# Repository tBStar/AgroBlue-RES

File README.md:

# AgroBlue
When BLE meets agronomy.

My idea is very simple yet ambitious. Imagine a fleet of BLE enabled soil probes working in harmony that can sense the environment and be able to communicate with a central unit. This central unit will be responsible for collecting data for analysis.

This proof of concept is the understanding of how the combination of all sensors reading correlate to each other, to maximize efficiency and increase crop yield in the open. Battery longevity and cost are my main goals, let's hope it will work out.

1st Step:(PCB)
---------
- Get your board fabricated! The Eagle files are provided as-is, without warranty of any kind so use it at your own risk!
I used https://oshpark.com/ for my fabrication shop because I heard so many positive reviews. I initially opted for the regular service which takes 3 weeks but they upgraded me for free because they had free room on one of our Super Swift Service panels, So thank you OSH Park.
 - Get the components, I've included the BOM but I will list them here for the sake of having everything in one page.

|Qty|Description|URL|Price|
|---|---|---|---|
|x 1|Coin Cell Battery Holders Linx CR2032 Battery Holder|http://www.mouser.com/search/ProductDetail.aspx?r=712-BAT-HLD-001|$0.25|
|x 1|Lithium Ion Polymer Battery 3.7V 350mAh|https://www.arrow.com/en/products/2750/adafruit-industries|$6.77|
|x 2|Res Thin Film 0805 100 Ohm 1% 0.25W (1/4W)|https://www.arrow.com/en/products/rncp0805ftd100r/stackpole-electronics|$0.0052|
|x 1|Cap Ceramic 0.1uF 16V X7R 10% Pad SMD 0805|https://www.arrow.com/en/products/cl21b104koannnd/samsung-electro-mechanics|$0.02|
|x 1|Trans GP BJT NPN 40V 0.6A 3-Pin SOT-23|https://www.arrow.com/en/products/mmbt2222alt3g/on-semiconductor|$0.02|
|x 1|Lithium Battery Coin 3V 225mAh|https://www.arrow.com/en/products/cr-2032lbn/panasonic|$0.18|
|x 1|SparkFun ESP8266 Thing - Dev Board|https://www.sparkfun.com/products/13711|$15.95|
|x 1|HM-10 BLE Module|https://www.aliexpress.com/item/HM-10-cc2541-4-0-BLE-bluetooth-to-uart-transceiver-Module-Central-Peripheral-switching-iBeacon-AirLocate/32460585727.html|$3.34|
|x 1|HM-10 BLE Module Breakout Board|https://www.aliexpress.com/item/Free-shipping-HM-10-Bluetooth-BLE-4-0-Module-transparent-serial-port-Bluetooth-4-0-module/1913999168.html|$4.75|

2nd Step:(Optional if you have BLE Module Clones)
-------------------------------------------------
If you've gotten yourself some HM-10 clones, fear not. The following is an effective way to upload the original firmware to the module. We are going to be using v540. the original files can be found here: https://github.com/RedBearLab/CCLoader.

1. Load the CCLoader Arduino sketch to the UNO board.
2. Wire the pins:
  
3. Use CCLoader.exe to load the CC2541hm10v540.bin to the UNO board and the board will burn the firmware to the BLE Mini.

3rd Step: (Configure BLE Modules Master/Slave)
----------------------------------------------

a) Slave:
Upload an empty sketch to Aruidno and hookup the sensor module with it like this:

HM-10||Arduino
|---|---|---|
TX|<---->|TX
RX|<---->|RX
GND|<---->|GND
VCC|<---->|3.3V

Open the serial and type the following command to switch the mode of transmission to remote:
AT+MODE2: Remote Control Mode
AT+ROLE0: Peripheral Mode (Default)
AT+PWRM0: Auto Sleep
AT+ADVIF: Set the advertising interval to 7s (MAX)
AT+NAMEXXX: Where XXX is your preferred name
AT+BAUD4: Set the baud rate to 115200
AT+RESET: Restart module

b) Master
Hook up the BLE Module Breakout board the same way as the Sensor per below and type the following commands:

On master side:
AT+RENEW: Restore all setup value to factory setup
AT+IMME1: Only respond the AT Commands
AT+ROLE1: Central/Master Mode
AT+NAMEXXX: Where XXX is your preferred name
AT+BAUD4: Set the baud rate to 115200
AT+RESET: Restart module

c) Upgrade firmware on genuine BLE module (Optional)
AT+VERR?: Will give you the version
For example, you need to be at least at V526 for analog support.

**HM-10** is designed and made by **JNHuaMao Technology Company**
More info on the upgrading process, visit http://www.jnhuamao.cn/

4th Step: (Getting the ESP8266 Dev Ready)
-----------------------------------------
1- Make sure you hookup the BLE Central/Master with the ESP8266 per below because we will be using SoftSerial library.

2- Use your Cayenne/Wifi credentials and upload main.ino located in Arduino/Code folder to the ESP8266. Open the serial and set it the baud rate to match your BLE Central.
	
3- Alternatively, you can use CentalBLEConfig.ino for debuging purposes. The code echos the serial input to the BLE and vice versa.
	
4- I found hooking up a lipo battery to the Slave BLE module works best because I found 3.3V is unusually lower for this kind of circuit. Make sure you don't hookup the cell and the lipo at the same time. There is no reverse current protection.
	
5- Water your plan and you should see some reading coming through your cloud interface through channel 0.

In Summary:
-----------
I thank all the sponsors that made this contest possible. Special thanks to Sparkfun for their gratuitous dev board. I made mamy mistakes a long the way but the experience and sense of accomplishment was beyond what I imagined. I hope my work can pave the way for a continuation for finding inovative ways to improve on my design to make the world a better place.
Res stands for resistive, the probes can corrode very easily which will require replacement. As is this iteration can only be used indoor. I've done current consumption readings:
Sleep mode: 20uA
Advertising: 80uA
Connected: 8mA
Moisture Sensing: ~100mA
I found out very inefficient compared to capacitive sensing which can consume about 5mA while sensing. Very interesting indeed.

Also, to harness the full power of any BLE module is to be able to program it myself. Most of the advanced BLE modules use a flavor of ARM Cortex M processors, since they are engineered for maximum power efficiency, it makes them the rightful candidates for my next project which will be called AgroBlue-Cap.
For outdoor usage, I highly recommend you apply silicone conformal coating because the module as is can be easily damaged by environmental elements. Ideally, I would enclose the circuitry in a water/moisture proof box and use an external antenna.

Tidbits:
--------
- Sparkfun originally shipped the wrong Wifi module. They later shipped the correct one, since it was a mistake, they let me keep both.
- OshPark upgraded my order to the express service for free which costs double and take a lot less, so thank you OshPark.
- The datasheet provided by JNHuaMao Technology Company has a serious mistake. PIN3 is listed as ADC compatible while it wasn't. So bonded PIN4 to it for immediate fix, the schematics has been corrected.
- Since I was rushing to get the project out, I accidently exposed my cayenne/wifi credentials. A fatal mistake but I got a good laugh at it, so always double check and don't rush.
- I am a first timer on all levels, contest, github, eagle, board fabrication, smd soldering, youtube publishing and video recording. Quite a story there.

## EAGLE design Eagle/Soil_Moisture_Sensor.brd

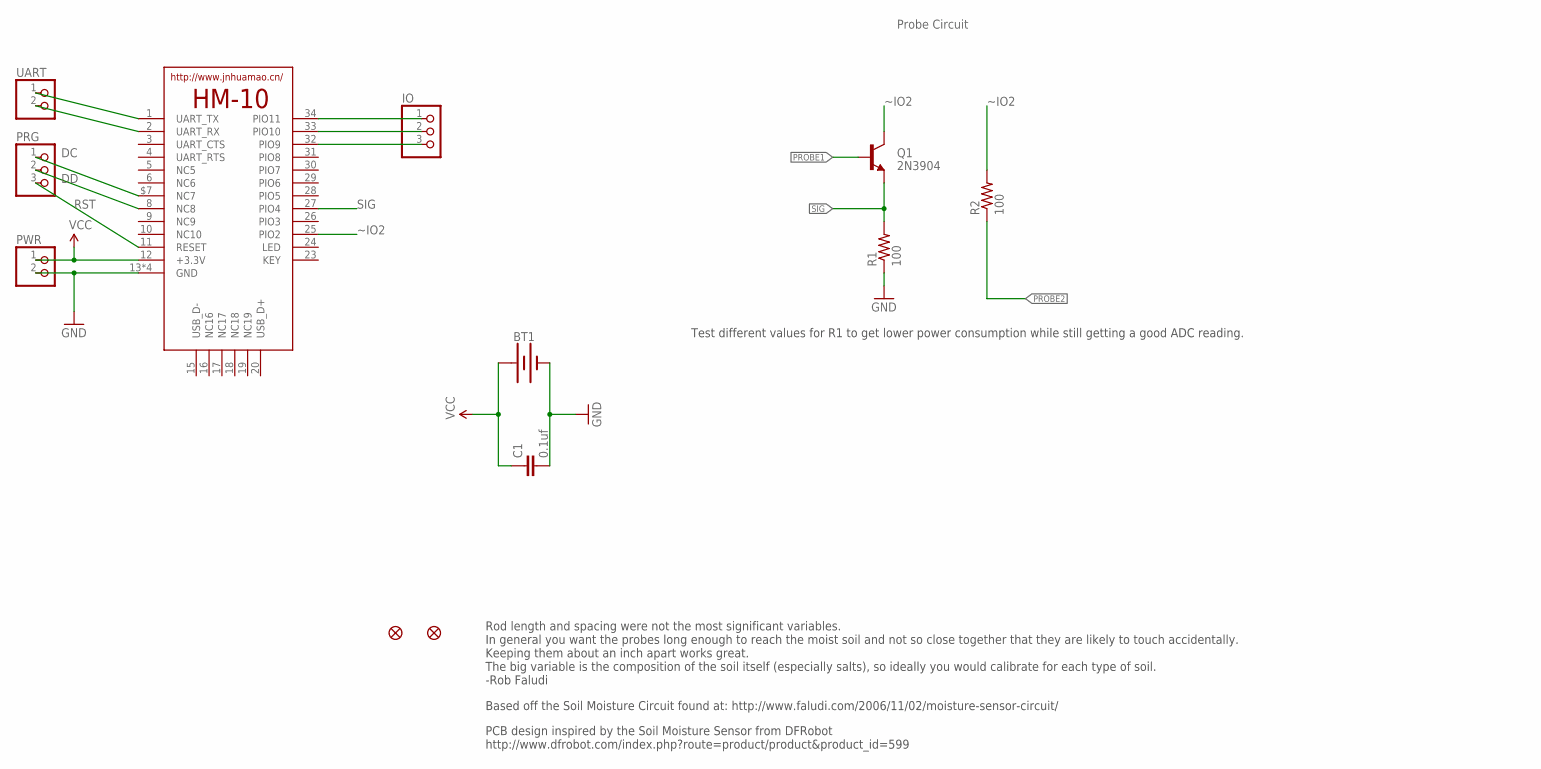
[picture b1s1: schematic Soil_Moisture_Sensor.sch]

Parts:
BT1: BATTERY-20MM_SMD_4LEGS; BATTCON_20MM_4LEGS
C1: 0.1uf; C0805
FD1, FD2: FIDUCIAL1X2; FIDUCIAL-1X2
HM-10: HM-10-BOARD; 26.9X13X2.2_BOARD
IO: PINHD-1X3; 1X03
PRG: PINHD-1X3; 1X03
PWR: PINHD-1X2; 1X02
Q1: 2N3904; SOT23-3
R1, R2: 100; R0805
UART: PINHD-1X2; 1X02

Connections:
DC: HM-10.$7 (NC7), PRG.1
DD: HM-10.8 (NC8), PRG.2
GND: BT1.NEGATIVE (-), C1.2, HM-10.13 (GND), HM-10.14 (GND), HM-10.21 (GND), HM-10.22 (GND), PWR.2, R1.1
unnamed: HM-10.34 (PIO11), IO.1
unnamed: HM-10.33 (PIO10), IO.2
unnamed: HM-10.32 (PIO9), IO.3
unnamed: HM-10.1 (UART_TX), UART.1
unnamed: HM-10.2 (UART_RX), UART.2
PROBE1: Q1.1 (B)
PROBE2: R2.1
RST: HM-10.11 (RESET), PRG.3
SIG: HM-10.27 (PIO4), Q1.2 (E), R1.2
VCC: BT1.POSITIVE@1 (+), BT1.POSITIVE@2 (+), BT1.POSITIVE@3 (+), BT1.POSITIVE@4 (+), C1.1, HM-10.12 (+3.3V), PWR.1
~IO2: HM-10.25 (PIO2), Q1.3 (C), R2.2

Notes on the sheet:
Test different values for R1 to get lower power consumption while still getting a good ADC reading.
Based off the Soil Moisture Circuit found at: http://www.faludi.com/2006/11/02/moisture-sensor-circuit/
Rod length and spacing were not the most significant variables. In general you want the probes long enough to reach the moist soil and not so close together that they are likely to touch accidentally. Keeping them about an inch apart works great. The big variable is the composition of the soil itse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
Probe Circuit
PCB design inspired by the Soil Moisture Sensor from DFRobot http://www.dfrobot.com/index.php?route=product/product&product_id=599

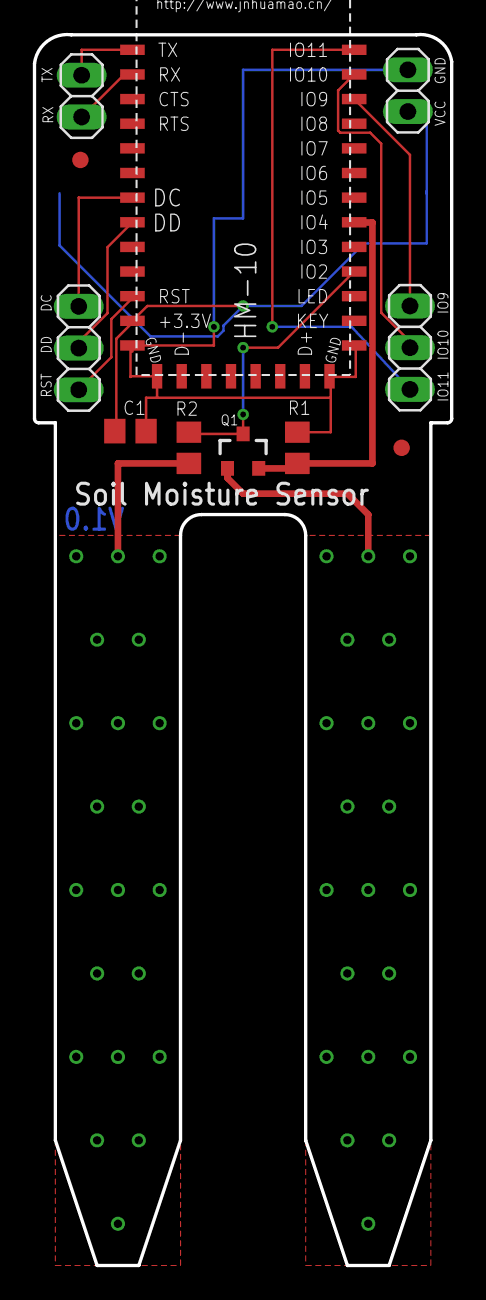
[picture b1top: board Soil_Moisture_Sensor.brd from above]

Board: 2 copper layers, 25.4 x 74.9 mm, 12 parts (1 on the bottom side), 12 nets.

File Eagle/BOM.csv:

"Part";"Value";"Device";"Package";"Description";"PROD_ID";"SF_SKU";"VALUE";
"BT1";"";"BATTERY-20MM_SMD_4LEGS";"BATTCON_20MM_4LEGS";"Battery - Single Cell";"BATT-10373";"PRT-11892";"";
"C1";"0.1uf";"C-EUC0805";"C0805";"CAPACITOR, European symbol";"";"";"";
"FD1";"FIDUCIAL1X2";"FIDUCIAL1X2";"FIDUCIAL-1X2";"Fiducial Alignment Points";"";"";"";
"FD2";"FIDUCIAL1X2";"FIDUCIAL1X2";"FIDUCIAL-1X2";"Fiducial Alignment Points";"";"";"";
"HM-10";"HM-10-BOARD";"HM-10-BOARD";"26.9X13X2.2_BOARD";"HM Bluetooth module use TI CC2540 or CC2541, Master and slave roles in one, transmission version and remote control version and PIO state acquisition functions in one, Support the AT command modify module parameters, Convenient and flexible.";"";"";"";
"IO";"";"PINHD-1X3";"1X03";"PIN HEADER";"";"";"";
"PRG";"";"PINHD-1X3";"1X03";"PIN HEADER";"";"";"";
"PWR";"";"PINHD-1X2";"1X02";"PIN HEADER";"";"";"";
"Q1";"2N3904";"TRANSISTOR_NPNMMBT2222A";"SOT23-3";"Generic NPN BJT";"TRANS-08049";"";"MMBT2222A";
"R1";"100";"100OHM-1/4W-5%(0603)";"0603-RES";"";"RES-12438";"";"100/.25W";
"R2";"100";"100OHM-1/4W-5%(0603)";"0603-RES";"";"RES-12438";"";"100/.25W";
"UART";"";"PINHD-1X2";"1X02";"PIN HEADER";"";"";"";

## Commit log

2017-10-19 Cleanup
2017-10-21 Added BLE Module's Eagle library file
2017-10-21 Added HM-10 Datasheet
2017-10-21 updagtes

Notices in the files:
parts and their libraries:
SparkFun-DiscreteSemi: Licensing: Creative Commons ShareAlike 4.0 International - https://creativecommons.org/licenses/by-sa/4.0
